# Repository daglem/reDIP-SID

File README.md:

# reDIP SID

## MOS 6581/8580 SID FPGA emulation platform

## Overview
The reDIP SID is an open source hardware development board which combines the following in a DIP-28 size package:

* Lattice iCE40UP5K FPGA
* NXP SGTL5000 Audio Codec
* 128Mbit FLASH
* 64Mbit PSRAM
* User LED
* Push button
* USB-C receptacle for power and FPGA Full Speed USB
* 5V tolerant I/O

The reDIP SID provides a fully functional open source hardware platform for MOS 6581/8580 SID emulation.

The reDIP SID also aims to be a good no-frills generic choice for FPGA projects which may find use for audio and/or 5V tolerant I/O -
it should be ideal for for e.g. retro computer and synthesizer projects.

Designs for the iCE40UP5K FPGA can be processed by [yosys](https://github.com/YosysHQ/yosys/) and [nextpnr](https://github.com/YosysHQ/nextpnr/).

The board is supported by the DFU [Nitro Bootloader](https://github.com/no2fpga/no2bootloader/), facilitating simple updates over USB using e.g. [dfu-util](http://dfu-util.sourceforge.net/).

## General use

### I/O interfaces

#### Header pins:

* 12V / 9V input (for SID audio output DC bias / C64 model detection)
* 5V input
* 19 FPGA GPIO
* 3 FPGA current drive / open-drain I/O
* 5 audio pins (stereo line input, stereo line output, SID audio output)
* GND

All FPGA header I/O is 5V tolerant, and can drive 5V TTL. JP1 can be shorted to make the 5V input pin bidirectional, e.g. to power 5V TTL devices from USB VBUS.

Note that the line inputs are not AC coupled - AC coupling must be externally added for audio applications.
Without external AC coupling, the line inputs can conceivably be used as generic ADCs.

The 12V / 9V input is connected to the SGTL5000 mic input via a 1/6 ratio voltage divider.

#### SPI / programming header:

A separate header footprint is provided for (Q)SPI peripherals / flash programming, with pinout borrowed from the [iCEBreaker Bitsy](https://github.com/icebreaker-fpga/icebreaker).

The header provides a 3.3V output, which may be used to power external devices. The 3.3V rail is supplied by a 700mA LDO.

#### USB-C functions:

* 5V power
* FPGA Full Speed USB

## MOS 6581/8580 SID compatibility

The board is fully pin compatible with the venerable MOS 6581/8580 SID sound chip.

The board features three additional address pins which may be connected to the Commodore 64, in order to make a second SID chip appear e.g. at address D420, D500, or DE00.

There is also an additional EXT IN audio input pin for a second SID chip, and separate stereo line output pins which may be connected directly to audio equipment.
Either the SID GND pin or GND on the programming header may be used as audio ground.

Cycle accurate emulation of the SID chip has been implemented in [gateware](gateware/).

## Thanks

Big thanks go to [Sylvain "tnt" Munaut](https://github.com/smunaut/), who has not only implemented support for the reDIP SID in his [Nitro Bootloader](https://github.com/no2fpga/no2bootloader/),
but has also identified shortcomings, suggested feature improvements, and provided invaluable help to ensure that the board actually works.

Thanks must also go to [Aidan Dodds](https://github.com/bit-hack) and [Paul Sajna](https://github.com/sajattack)
for putting the first prototype through its paces working on Dodds' [icesid](https://github.com/bit-hack/icesid), with guidance from Munaut.

## Board Front

## Board Back

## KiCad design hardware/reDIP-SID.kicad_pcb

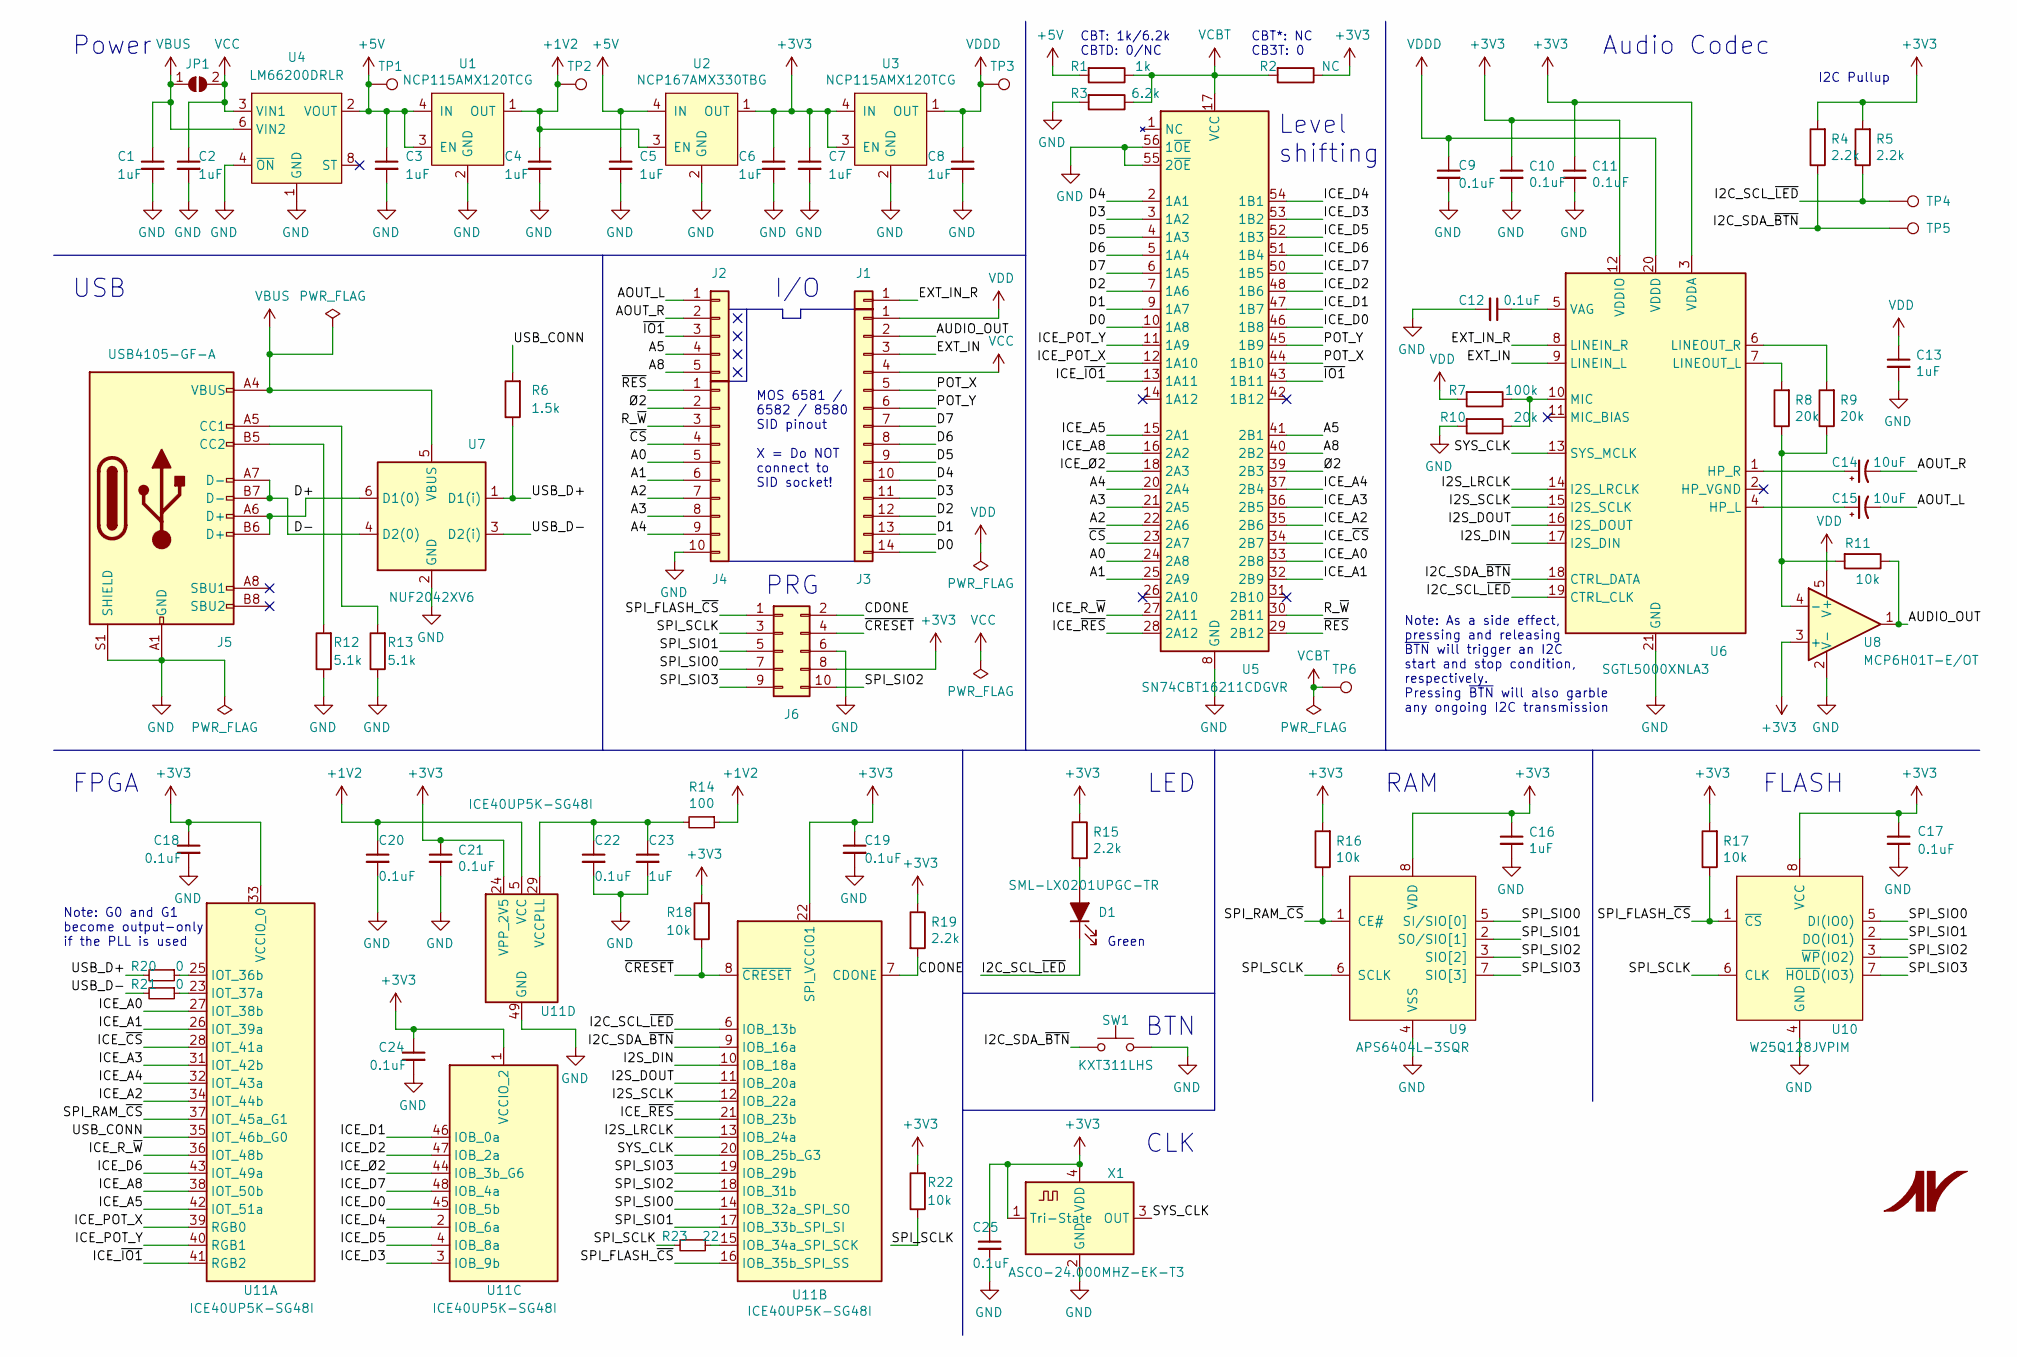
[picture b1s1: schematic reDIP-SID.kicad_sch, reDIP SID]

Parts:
C1, C2, C3, C5: 1uF; C_0402_1005Metric
C4, C6, C7, C8, C16, C23: 1uF; C_0201_0603Metric
C9, C10, C11, C12, C17, C18, C19, C20, C21, C22, C24, C25: 0.1uF; C_0201_0603Metric
C13: 1uF; C_0603_1608Metric
C14, C15: 10uF; CP_EIA-1608-08_AVX-J
D1: SML-LX0201UPGC-TR; SML-LX0201
J1: Conn_01x01; PinHeader_1x01_P2.54mm_Vertical
J2: Conn_01x05; PinHeader_1x05_P2.54mm_Vertical
J3: Conn_01x14; PinHeader_1x14_P2.54mm_Vertical_Machined
J4: Conn_01x10; PinHeader_1x10_P2.54mm_Vertical_Machined
J5: USB4105-GF-A; USB_C_Receptacle_HRO_TYPE-C-31-M-12
J6: Conn_02x05_Odd_Even; PinHeader_2x05_P2.54mm_Vertical
JP1: SolderJumper_2_Open; R_0402_1005Metric
R1: 1k; R_0201_0603Metric
R2: NC; R_0201_0603Metric
R3: 6.2k; R_0201_0603Metric
R4, R5, R15, R19: 2.2k; R_0201_0603Metric
R6: 1.5k; R_0201_0603Metric
R7: 100k; R_0201_0603Metric
R8, R9, R10: 20k; R_0201_0603Metric
R11, R16, R17, R18, R22: 10k; R_0201_0603Metric
R12, R13: 5.1k; R_0201_0603Metric
R14: 100; R_0201_0603Metric
R20, R21: 0; R_0201_0603Metric
R23: 22; R_0201_0603Metric
SW1: KXT311LHS; SW_SPST_CK_KXT3
TP1, TP2, TP3, TP4, TP5, TP6: TestPoint; TestPoint_Pad_D0.75mm
U1, U3: NCP115AMX120TCG; CASE_711AJ_1.0x1.0mm_P0.65mm
U2: NCP167AMX330TBG; CASE_711AJ_1.0x1.0mm_P0.65mm
U4: LM66200DRLR; SOT-5X3
U5: SN74CBT16211CDGVR; Texas_TVSOP-56_4.4x11.3mm_P0.4mm
U6: SGTL5000XNLA3; QFN-20-1EP_3x3mm_P0.4mm_EP1.65x1.65mm
U7: NUF2042XV6; SOT-563
U8: MCP6H01T-E/OT; SOT-23-5
U9: APS6404L-3SQR; SOP-8_3.9x4.9mm_P1.27mm
U10: W25Q128JVPIM; WSON-8-1EP_6x5mm_P1.27mm_EP3.4x4.3mm
U11: ICE40UP5K-SG48I; QFN-48-1EP_7x7mm_P0.5mm_EP5.6x5.6mm
X1: ASCO-24.000MHZ-EK-T3; Oscillator_SMD-4Pin_1.6x1.2mm

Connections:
+1V2: C4.1, C20.1, R14.1, TP2.1, U1.1 (OUT), U2.3 (EN), U11.5 (VCC), U11.30 (VCC)
+3V3: C6.1, C7.1, C10.1, C11.1, C16.1, C17.1, C18.1, C19.1, C21.1, C24.1, C25.1, J6.8, R2.1, R4.2, R5.2, R15.1, R16.2, R17.2, R18.2, R19.1, R22.2, U2.1 (OUT), U3.3 (EN), U3.4 (IN), U6.3 (VDDA), U6.12 (VDDIO), U8.3 (+), U9.8 (VDD), U10.8 (VCC), U11.1 (VCCIO_2), U11.22 (SPI_VCCIO1), U11.24 (VPP_2V5), U11.33 (VCCIO_0), X1.1 (Tri-State), X1.4 (VDD)
+5V: C3.1, C5.1, R1.2, TP1.1, U1.3 (EN), U1.4 (IN), U2.4 (IN), U4.2 (VOUT), U4.7 (VOUT)
/A0: J4.5, U5.24 (2A8)
/A1: J4.6, U5.25 (2A9)
/A2: J4.7, U5.22 (2A6)
/A3: J4.8, U5.21 (2A5)
/A4: J4.9, U5.20 (2A4)
/A5: J2.4, U5.41 (2B1)
/A8: J2.5, U5.40 (2B2)
/AOUT_L: C15.2, J2.1
/AOUT_R: C14.2, J2.2
/AUDIO_OUT: J3.2, R11.1, U8.1
/CDONE: J6.2, R19.2, U11.7 (CDONE)
/D0: J3.14, U5.10 (1A8)
/D1: J3.13, U5.9 (1A7)
/D2: J3.12, U5.7 (1A6)
/D3: J3.11, U5.3 (1A2)
/D4: J3.10, U5.2 (1A1)
/D5: J3.9, U5.4 (1A3)
/D6: J3.8, U5.5 (1A4)
/D7: J3.7, U5.6 (1A5)
/D+: J5.A6 (D+), J5.B6 (D+), U7.6 (D1(0))
/D-: J5.A7 (D-), J5.B7 (D-), U7.4 (D2(0))
/EXT_IN: J3.3, U6.9 (LINEIN_L)
/EXT_IN_R: J1.1, U6.8 (LINEIN_R)
/I2C_SCL_~LED: D1.1 (K), R5.1, TP4.1, U6.19 (CTRL_CLK), U11.6 (IOB_13b)
/I2C_SDA_~BTN: R4.1, SW1.1, TP5.1, U6.18 (CTRL_DATA), U11.9 (IOB_16a)
/I2S_DIN: U6.17 (I2S_DIN), U11.10 (IOB_18a)
/I2S_DOUT: U6.16 (I2S_DOUT), U11.11 (IOB_20a)
/I2S_LRCLK: U6.14 (I2S_LRCLK), U11.13 (IOB_24a)
/I2S_SCLK: U6.15 (I2S_SCLK), U11.12 (IOB_22a)
/ICE_A0: U5.33 (2B8), U11.27 (IOT_38b)
/ICE_A1: U5.32 (2B9), U11.26 (IOT_39a)
/ICE_A2: U5.35 (2B6), U11.34 (IOT_44b)
/ICE_A3: U5.36 (2B5), U11.31 (IOT_42b)
/ICE_A4: U5.37 (2B4), U11.32 (IOT_43a)
/ICE_A5: U5.15 (2A1), U11.42 (IOT_51a)
/ICE_A8: U5.16 (2A2), U11.38 (IOT_50b)
/ICE_D0: U5.46 (1B8), U11.45 (IOB_5b)
/ICE_D1: U5.47 (1B7), U11.46 (IOB_0a)
/ICE_D2: U5.48 (1B6), U11.47 (IOB_2a)
/ICE_D3: U5.53 (1B2), U11.3 (IOB_9b)
/ICE_D4: U5.54 (1B1), U11.2 (IOB_6a)
/ICE_D5: U5.52 (1B3), U11.4 (IOB_8a)
/ICE_D6: U5.51 (1B4), U11.43 (IOT_49a)
/ICE_D7: U5.50 (1B5), U11.48 (IOB_4a)
/ICE_POT_X: U5.12 (1A10), U11.39 (RGB0)
/ICE_POT_Y: U5.11 (1A9), U11.40 (RGB1)
/ICE_R_~W: U5.27 (2A11), U11.36 (IOT_48b)
/ICE_~CS: U5.34 (2B7), U11.28 (IOT_41a)
/ICE_~IO1: U5.13 (1A11), U11.41 (RGB2)
/ICE_~RES: U5.28 (2A12), U11.21 (IOB_23b)
/ICE_Ø2: U5.18 (2A3), U11.44 (IOB_3b_G6)
/POT_X: J3.5, U5.44 (1B10)
/POT_Y: J3.6, U5.45 (1B9)
/R_~W: J4.3, U5.30 (2B11)
/SPI_FLASH_~CS: J6.1, R17.1, U10.1 (~CS), U11.16 (IOB_35b_SPI_SS)
/SPI_RAM_~CS: R16.1, U9.1 (CE#), U11.37 (IOT_45a_G1)
/SPI_SCLK: J6.3, R22.1, R23.2, U9.6 (SCLK), U10.6 (CLK)
/SPI_SIO0: J6.7, U9.5 (SI/SIO[0]), U10.5 (DI(IO0)), U11.14 (IOB_32a_SPI_SO)
/SPI_SIO1: J6.5, U9.2 (SO/SIO[1]), U10.2 (DO(IO1)), U11.17 (IOB_33b_SPI_SI)
/SPI_SIO2: J6.10, U9.3 (SIO[2]), U10.3 (~WP(IO2)), U11.18 (IOB_31b)
/SPI_SIO3: J6.9, U9.7 (SIO[3]), U10.7 (~HOLD(IO3)), U11.19 (IOB_29b)
/SYS_CLK: U6.13 (SYS_MCLK), U11.20 (IOB_25b_G3), X1.3 (OUT)
/USB_CONN: R6.2, U11.35 (IOT_46b_G0)
/USB_D+: R6.1, R20.2, U7.1 (D1(i))
/USB_D-: R21.2, U7.3 (D2(i))
/~CRESET: J6.4, R18.1, U11.8 (~CRESET)
/~CS: J4.4, U5.23 (2A7)
/~IO1: J2.3, U5.43 (1B11)
/~RES: J4.1, U5.29 (2B12)
/Ø2: J4.2, U5.39 (2B3)
GND: C1.2, C2.2, C3.2, C4.2, C5.2, C6.2, C7.2, C8.2, C9.2, C10.2, C11.2, C12.2, C13.2, C16.2, C17.2, C18.2, C19.2, C20.2, C21.2, C22.2, C23.2, C24.2, C25.2, J4.10, J5.A1 (GND), J5.A12 (GND), J5.B1 (GND), J5.B12 (GND), J5.S1 (SHIELD), J6.6, R3.2, R10.2, R12.1, R13.1, SW1.2, U1.2 (GND), U2.2 (GND), U3.2 (GND), U4.1 (GND), U4.4 (~ON), U4.5 (GND), U5.8 (GND), U5.19 (GND), U5.38 (GND), U5.49 (GND), U5.55 (2~OE), U5.56 (1~OE), U6.21 (GND), U7.2 (GND), U8.2 (V-), U9.4 (VSS), U10.4 (GND), U10.9 (GND), U11.49 (GND), X1.2 (GND)
unnamed: D1.2 (A), R15.2
unnamed: J5.A5 (CC1), R13.2
unnamed: J5.B5 (CC2), R12.2
unnamed: C15.1, U6.4 (HP_L)
unnamed: C14.1, U6.1 (HP_R)
unnamed: R8.2, U6.7 (LINEOUT_L)
unnamed: R9.2, U6.6 (LINEOUT_R)
unnamed: R7.1, R10.1, U6.10 (MIC)
unnamed: C12.1, U6.5 (VAG)
unnamed: R8.1, R9.1, R11.2, U8.4 (-)
unnamed: R20.1, U11.25 (IOT_36b)
unnamed: R21.1, U11.23 (IOT_37a)
unnamed: R23.1, U11.15 (IOB_34a_SPI_SCK)
unnamed: C22.1, C23.1, R14.2, U11.29 (VCCPLL)
VBUS: C1.1, J5.A4 (VBUS), J5.A9 (VBUS), J5.B4 (VBUS), J5.B9 (VBUS), JP1.1 (A), U4.6 (VIN2), U7.5 (VBUS)
VCBT: R1.1, R2.2, R3.1, TP6.1, U5.17 (VCC)
VCC: C2.1, J3.4, JP1.2 (B), U4.3 (VIN1)
VDD: C13.1, J3.1, R7.2, U8.5 (V+)
VDDD: C8.1, C9.1, TP3.1, U3.1 (OUT), U6.20 (VDDD)

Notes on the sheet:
MOS 6581 / 6582 / 8580 SID pinout X = Do NOT connect to SID socket!
Note: As a side effect, pressing and releasing ~{BTN} will trigger an I2C start and stop condition, respectively. Pressing ~{BTN} will also garble any ongoing I2C transmission
PRG
FLASH
FPGA
USB
RAM
CLK
Power
Green
CBT*: NC CB3T: 0
BTN
LED
I/O
Level shifting
Audio Codec
CBT: 1k/6.2k CBTD: 0/NC
Note: G0 and G1 become output-only if the PLL is used
I2C Pullup

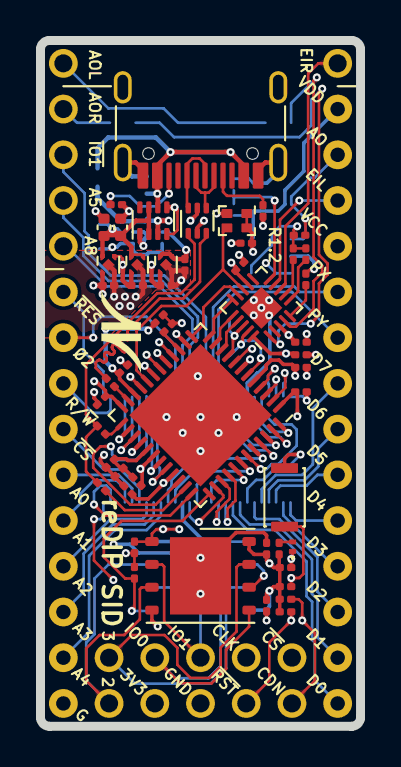
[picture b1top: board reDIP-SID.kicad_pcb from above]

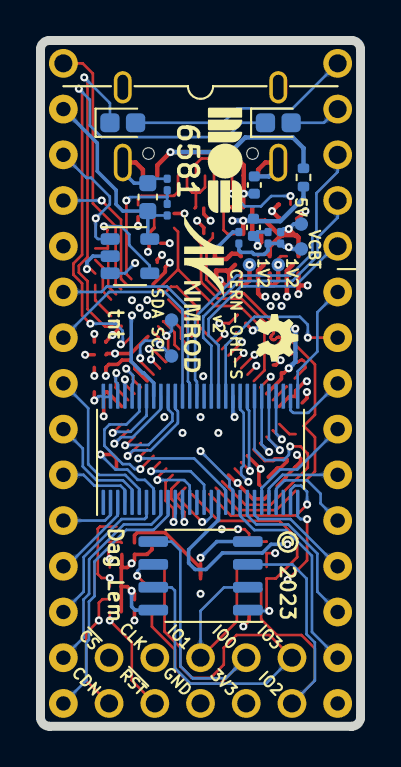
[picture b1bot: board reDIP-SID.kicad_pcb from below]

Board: 4 copper layers, 17.8 x 38.1 mm, 100 parts (42 on the bottom side), 93 nets.

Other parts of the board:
MOS logo: G***; MOS-logo
SolderMask_D0.5mm, SolderMask_D0.5mm#2, SolderMask_D0.5mm#3, SolderMask_D0.5mm#4, SolderMask_D0.5mm#5: SolderMask_D0.5mm
SolderMask_D0.25mm, SolderMask_D0.25mm#2, SolderMask_D0.25mm#3, SolderMask_D0.25mm#4, SolderMask_D0.25mm#5, SolderMask_D0.25mm#6, SolderMask_D0.25mm#7, SolderMask_D0.25mm#8, SolderMask_D0.25mm#9, SolderMask_D0.25mm#10, SolderMask_D0.25mm#11, SolderMask_D0.25mm#12, SolderMask_D0.25mm#13, SolderMask_D0.25mm#14, SolderMask_D0.25mm#15, SolderMask_D0.25mm#16, SolderMask_D0.25mm#17, SolderMask_D0.25mm#18, SolderMask_D0.25mm#19: SolderMask_D0.25mm

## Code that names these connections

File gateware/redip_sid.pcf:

# Pin Constraints File for reDIP SID - iCE40UP5K-SG48I

# Clock frequencies (nextpnr only)
set_frequency sys_clk 24.0
set_frequency i2s_sclk 6.144  # 64 * 96kHz
# set_frequency usb_clk 48.0

# System clock
set_io -nowarn sys_clk 20

# I2C + button / LED (shared)
set_io -nowarn i2c_scl_led_n 6
set_io -nowarn i2c_sda_btn_n 9

# I2S
set_io -nowarn i2s_din   10
set_io -nowarn i2s_dout  11
set_io -nowarn i2s_sclk  12
set_io -nowarn i2s_lrclk 13

# SPI
set_io -nowarn spi_sio0       14  # MOSI
set_io -nowarn spi_sio1       17  # MISO
set_io -nowarn spi_sio2       18
set_io -nowarn spi_sio3       19
set_io -nowarn spi_clk        15
set_io -nowarn spi_flash_cs_n 16
set_io -nowarn spi_ram_cs_n   37

# USB
set_io -nowarn usb_d_p  25
set_io -nowarn usb_d_n  23
set_io -nowarn usb_conn 35

# SID I/O

# SID address bus (A0-A4)
set_io -nowarn a0 27
set_io -nowarn a1 26
set_io -nowarn a2 34
set_io -nowarn a3 31
set_io -nowarn a4 32

# SID data bus (D0-D7)
set_io -nowarn d0 45
set_io -nowarn d1 46
set_io -nowarn d2 47
set_io -nowarn d3  3
set_io -nowarn d4  2
set_io -nowarn d5  4
set_io -nowarn d6 43
set_io -nowarn d7 48

# SID R/W
set_io -nowarn r_w_n 36

# SID CS
set_io -nowarn cs_n     28
# Extra chip select
set_io -nowarn cs_io1_n 41
# Extra address pins
set_io -nowarn a5       42
set_io -nowarn a8       38

# SID Ø2 (master clock)
set_io -nowarn phi2 44

# SID RES
set_io -nowarn res_n 21

# SID A/D converter inputs
set_io -nowarn pot_x 39
set_io -nowarn pot_y 40

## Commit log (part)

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2021-01-11 Moved Vcc via away from pin-in-paste stencil aperture
2021-01-13 Usability and manufacturability improvements
    * Made all iCE40 RGB pins externally available
    * Removed split in stencil apertures for pin-in-paste
2021-01-13 Re-added JP1 on back silk screen
2021-01-17 Usability and manufacturability improvements
    * Added extra vias for Vcc and 3.3V rails, for high power external devices
    * Added extra thermal via for SGTL5000
    * Assume 3x solder paste volume for paste-in-hole
    * Adjustments to fab and silk screen layers
2021-01-17 Changed title
2021-01-19 Updated link to reDIP SX
2021-03-04 Various fixes
    * Added 10k pullup for SPI SCLK, following iCE40 Hardware Checklist
    * Reworked USB routing to not rely on any particular ESD IC (note swapped pins)
    * Widened a few tracks
    * Added silk screen on back side for SPI header
    * Increased courtyard for TVSOP-56 footprint
    * Changed VCC to power symbol
2021-03-04 Remember to add ray tracing for board image
    Is it possible to script output from the 3D viewer?
2021-04-18 Replaced non-stocked parts
    * Replaced 1.2V LDO with more readily available part
    * Changed oscillator reeling order number
2021-04-21 Attempt at reducing layer count from 6 to 4
2021-04-21 Removed splits in ground on layer In2.Cu, removed ground pour on layer B.Cu
    Changes suggested by zyp.
2021-04-24 Showstopper fixes
    * Pins swaps and rerouting to handle the fact that iCE40UP5K pins 35 and 37
    are output only when the PLL is used
    * Removed Q1, USB_CONN is now used to pull up USB D+ directly through R3
    * Changed the oscillator to 24 MHz (full speed USB is clocked at 12 MHz)
    * Slight rounding of footprint pads for oscillator and button
    Many thanks go to @smunaut for pointing out the (undocumented!) iCE40 PLL
2021-04-25 Preparing for prototyping
    * Routing cleanups
    * Changed oscillator to ± 25 ppm part
    * Note on the PLL output-only-pin trap in the schematic
    Thanks to @DX-MON for pointing out that audio hardware should have
    as high frequency stability as possible.
2021-04-27 Improved decoupling
    * Improved decoupling and PLL power filtering, as suggested by @smunaut
    * Minor cleanups on F.Fab layer
    * Added note in the schematic on the side effects of pressing the user button
2021-04-27 Files for manufacture
    * Added note on pin-in-paste for USB-C connector
    * Capped component position resolution to 0.01mm
    * Moved kicost BOM spreadsheet to documentation/
    * Files for fabrication and assembly generated by KiKit
2021-04-28 Corrected files for manufacture
    "kikit fab pcbway" currently does not align layers and drills
    for designs with a specified auxiliary axis origin.
    For now, I have corrected this by making local changes to KiKit.
    Files for inner layers are also named to be consistent with
    outer layers, and are included in the .gbrjob file.
    Thanks to @DX-MON for the invaluable tip on re-checking the
2021-08-16 Revision 1.0
    The board has been revised to remedy a few shortcomings on the first prototype:
    * Added a separate LDO for the SGTL5000 VDDD, to keep the iCE40 VCC at 1.2V.
    * Added DC bias for AUDIO_OUT, required by the C64 audio output stage.
    * Increased board length by 2.54mm, facilitating some notable enhancements:
    - Symmetric stereo input (EXT_IN and EXT_IN_R). Note: External AC coupling.
    - Symmetric stereo output (AOUT_L and AOUT_R) in addition to AUDIO_OUT.
2021-08-18 Hardware mixing of left and right channels to AUDIO_OUT
    As suggested by @smunaut.
2021-08-21 Changed to machined (round) pin headers
    This allows the board to be mounted directly in a SID socket.
    Thanks to @smunaut for the pin header 3D models.
2021-08-28 Final major changes
    * Replaced Schottky diodes with power switch, minimizing 5V rail voltage drop.
    * Allow for measurement of VDD on SGTL5000 MIC input, as suggested by @smunaut.
    * Adjustments to the USB-C receptacle footprint, based on 2015 and 2020
    HRO TYPE-C-31-M-12 drawings, and the 2019 GCT USB4105 drawing.
2021-08-28 Added back JP1
    Thanks to @smunaut for the suggestion of jumpering VBUS and VCC
    instead of 5V and VCC, making JP1 compatible with the power switch.
2021-08-31 Added silkscreen polarity marking for tantalum capacitors
2021-09-02 Minor updates
    * Dimmer blue CDONE LED
    * BOM QA
2021-09-02 Updated PCB from Schematic wrt. change of (invisible) resistor value
2021-09-02 Fixed missing links on @mentions
2021-09-03 Added ngspice simulation for C64 audio output
2021-09-03 Revision 1.0
    This revision rounds off the features of the board, both as a drop-in
    SID replacement, and as a generic FPGA platform for audio and / or 5V
    tolerant I/O:
    * Fully 6581 / 8580 pin compatible
    * Machined (round) socket pin headers, for mounting directly in a SID socket
    * C64 model detection by measurement of VDD on SGTL5000 MIC input
2021-09-03 Update of schematic pdf
2021-09-09 Tweaks before manufacture
    * Added test point for 5V rail
    * Got rid of one BOM line by changing the MIC voltage divider
2021-09-13 Made all test points equal
2021-09-14 Modified ESD protection footprint to accomodate other SOT-563 / SOT-666 devices
2021-09-16 Marked position for UL and date code
2022-01-19 Migrated to KiCad 6
2022-02-16 Revision 1.1
    A few simplifications and tweaks.
    * Replaced FPF1321 with LM66200, removing a total of four components
    * Changed CDONE LED to turn on initially, and turn off after configuration
    * Moved date code to board front
    * Silk screen updates
2022-02-20 Update of pin header model from @smunaut
2022-02-20 Reduced soldermask opening diameter for all encroached BTC thermal vias
2022-02-21 Added missing file, updated board images
2022-02-27 Updated remaining local footprints to new format
2022-03-26 Removed unused SOT-883 footprint
2022-03-26 Revision 1.1
    * Changed PSRAM back from LY68L6400SLIT to APS6404L-3SQR
    * Changed USB-C receptacle from HRO TYPE-C-M-12-31 to GCT USB4105-GF-A
    * Replaced FPF1321 with LM66200, removing a total of four components
    * Changed CDONE LED to turn on initially, and turn off after configuration
    * Reduced soldermask opening diameter for all encroached BTC thermal vias
    * Moved fabrication date code to board front
2022-04-08 Revision 1.1 enhancements
    * Added input capacitors for LM66200
    * Changed bus switch to SN74CBT16211A, voltage divider bias for level shifting
    * Routing and power plane cleanups
2022-04-15 Board support for CBT, CBTD, and CB3T bus switches
2022-05-30 Added LICENSE file
2022-05-30 Start of gateware
    This is a first attempt at an implementation of the 6581 DACs in SystemVerilog.
    Unfortunately this currently doesn't work with Yosys, since it cannot handle
    variables of data type real in initial constructs.
2022-06-01 Precalculated DAC tables for Yosys
2022-10-02 MOS6581 / MOS8580 FPGA design
    This is a work in progress. The gateware is designed by someone who
    has never attempted a more advanced FPGA design than a "blinky", and
    nothing is tested, or even simulated. It goes without saying that the
    probability that anything will currently work is approximately 0.
    The design aims to be 100% cycle accurate, based on information from
    https://github.com/libsidplayfp/SID_schematics/wiki and
2022-10-02 Lookup table for tanh(x) instead of 1 + tanh(x)
2022-10-02 Added titles to filter cutoff curve plot
2022-10-02 Added .gitattributes for Linguist language detection
2022-10-02 Removed Verilog from .gitattributes
2022-10-02 Remove KiCad as language again
2022-10-02 Use extension .svh for included files
2022-10-02 Clarification on the use of tanh(-x) = -tanh(x)
2022-10-04 OSC3 is the output from the waveform selector, not from the waveform DAC
2022-10-04 Corrected clocking of the noise LFSR
2022-10-05 Preparations for simulation
2022-10-05 Corrected the voice DCA
2022-10-08 There is sound in simulation
    No working filter yet, though.
2022-10-10 The filter is now working
2022-10-11 Corrected addition of waveform DC
    Also be explicit about the voice outputs being 22 bits.
2022-10-18 Keep filter states internal to sid_filter module
    This necessitates the introduction of sv2v, since Yosys doesn't
    currently support arrays of structs, and I couldn't find any good
    workaround in this case.
2022-10-20 Avoid muxing of filter states
    This also removes the requirement of sv2v.
2022-10-24 Registered IO for I2S, unmute ADC
2022-10-27 And there was sound!
    * sv2v is used for preprocessing by default - there seems to be a
    SystemVerilog bug in Yosys, which causes only noise to be output.
    * Corrected timing for I2S, yielding clean sound output.
    * Temporarily put both SIDs at D400, pending runtime configuration.
2022-11-05 Combined waveforms including pulse are silent unless pulse is high
2022-11-06 Temporarily make both SIDs 6581s, pending runtime configuration
2022-11-13 Corrected expression for VOICE_DC_6581
    Yosys and Verilator interpret 32'('sh800*'shff) as
    32'sh00000800*32'sh000000ff, while sv2v and iverilog interpret
    the same expression as 32'shfffff800*32'shffffffff
2022-11-18 Speed up simulation of DACs
2022-11-19 Audo simulation improvements
    * Enable the C64 external filter by default
    * Properly initialize the C64 external filter
    * Exit if the standard input is a terminal
2022-11-21 Improved noise LFSR implementation
    * Corrected behavior of test bit set / release
    * Reset of LFSR when test or reset is held for some time
    * Writeback of zeros to output bits of LFSR for combined waveforms
2022-11-21 Reduced voice DC offset
    This brings the amplitude of volume samples relative to regular
    waveforms into the right ballpark.
2022-11-26 Elaborate a bit on the simulated external filter
2022-12-11 GitHub workflow for gateware releases
2023-03-16 Simplified generation of DAC bitsums
2023-03-16 Facilitate linting and Verilation of the complete design
2023-03-16 Alternative linting with slang
2023-03-21 Configurable LFSR envelope counter logic
2023-03-22 Use only two clock phases in the waveform generator
2023-03-24 Removed dummy clock phase PHI1_PHI2
2023-04-01 The noise LFSR was clocked one cycle too late
2023-04-03 Corrected MOS8580 triangle waveform timing for onset and ring modulation
2023-04-04 Updated OSS CAD Suite
2023-04-05 Corrected muacm boot
2023-04-06 Simplified procedure for flashing when μACM is not configured
    If μACM is not configured, drop into the bootloader on detection
    of a physical USB connection.
    Thanks to @sorgelig for the idea.
2023-05-06 Pipelining
    This is a major rewrite, pipelining all modules in the SID chip in order to
    save FPGA resources:
    * Power-on initialization of oscillators, noise LFSRs, and envelope counters
    * Register writes
    * Update and synchronization of oscillators
    * Waveform generation
2023-05-07 Lint fix
2023-05-07 Corrected envelope count delay
2023-05-09 Save ~20 LCs
2023-05-15 Waveform writeback
    * Zeroing of the 6581 oscillator MSB via combined waveforms
    * Zeroing of noise LFSR bits via combined waveforms
    Avoid additional storage for oscillator and noise LFSR states by
    freewheeling rotation.
2023-05-17 File rename
2023-05-19 Save / restore I flag on call to CHROUT
2023-05-19 Program to correctly sample 6581 pulse + sawtooth
2023-05-23 Corrected 8580 waveform 0, improved framework for noise LFSR writeback
2023-05-28 Corrected noise LFSR writeback
2023-05-29 Meet timing for no2muacm
2023-05-29 Keep within timing budget of 20 cycles
    Only one pause of the voice pipeline is needed, the second pause
    only served to simplify debugging with simulation.
2023-06-18 Sample all 6581 combined waveforms
    All combined waveforms which include sawtooth are affected by
    writeback to oscillator bit 23.
    Sample all combined waveforms except those which include noise.

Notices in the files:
hardware/reDIP-SID.kicad_pcb:
© 2021-2023 Dag Lem
Licensed under CERN-OHL-S v2 (https://ohwr.org/cern_ohl_s_v2.txt)
© 2023
CERN-OHL-S
